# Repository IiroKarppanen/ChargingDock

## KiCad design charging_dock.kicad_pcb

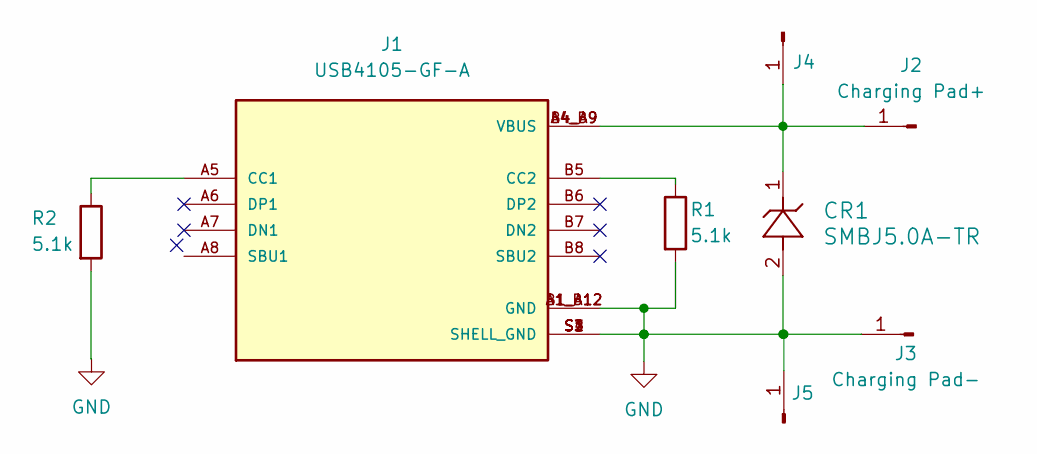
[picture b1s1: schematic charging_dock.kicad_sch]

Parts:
CR1: SMBJ5.0A-TR; SMB_STM
J1: USB4105-GF-A; GCT_USB4105-GF-A; PARTREV A3
J2: Charging Pad+; power_pad_5mm
J3: Charging Pad-; power_pad_5mm
J4, J5: Charging Pad+; PinHeader_1x01_P2.54mm_Vertical
R1, R2: 5.1k; R_0603_1608Metric

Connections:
GND: CR1.2, J1.A1_B12 (GND), J1.B1_A12 (GND), J1.S1 (SHELL_GND), J1.S2 (SHELL_GND), J1.S3 (SHELL_GND), J1.S4 (SHELL_GND), J3.1, J5.1, R1.2, R2.2
unnamed: J1.A5 (CC1), R2.1
unnamed: J1.B5 (CC2), R1.1
unnamed: CR1.1, J1.A4_B9 (VBUS), J1.B4_A9 (VBUS), J2.1, J4.1

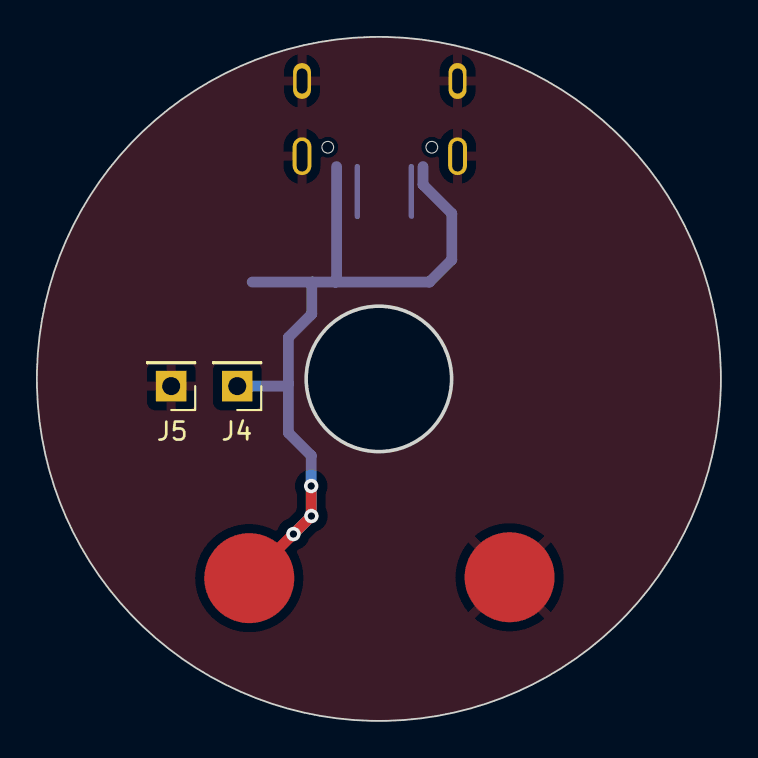
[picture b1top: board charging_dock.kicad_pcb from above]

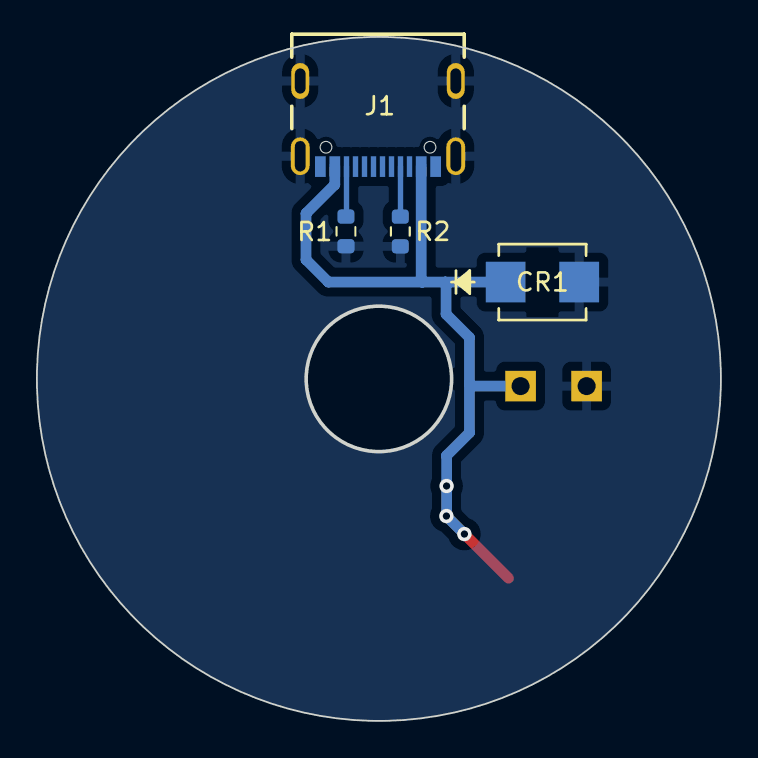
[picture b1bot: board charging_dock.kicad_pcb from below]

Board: 2 copper layers, 37.9 x 37.9 mm, 8 parts (4 on the bottom side), 4 nets.

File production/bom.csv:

Designator,Footprint,Quantity,Value,LCSC Part #
CR1,SMB_STM,1,SMBJ5.0A-TR,
J1,GCT_USB4105-GF-A,1,USB4105-GF-A,
J2,power_pad_5mm,1,Charging Pad+,
J3,power_pad_5mm,1,Charging Pad-,
"J4, J5",PinHeader_1x01_P2.54mm_Vertical,2,Charging Pad+,
"R1, R2",0603,2,5.1k,

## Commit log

2023-11-13 complete
2023-11-13 added hole for hr-sensor
